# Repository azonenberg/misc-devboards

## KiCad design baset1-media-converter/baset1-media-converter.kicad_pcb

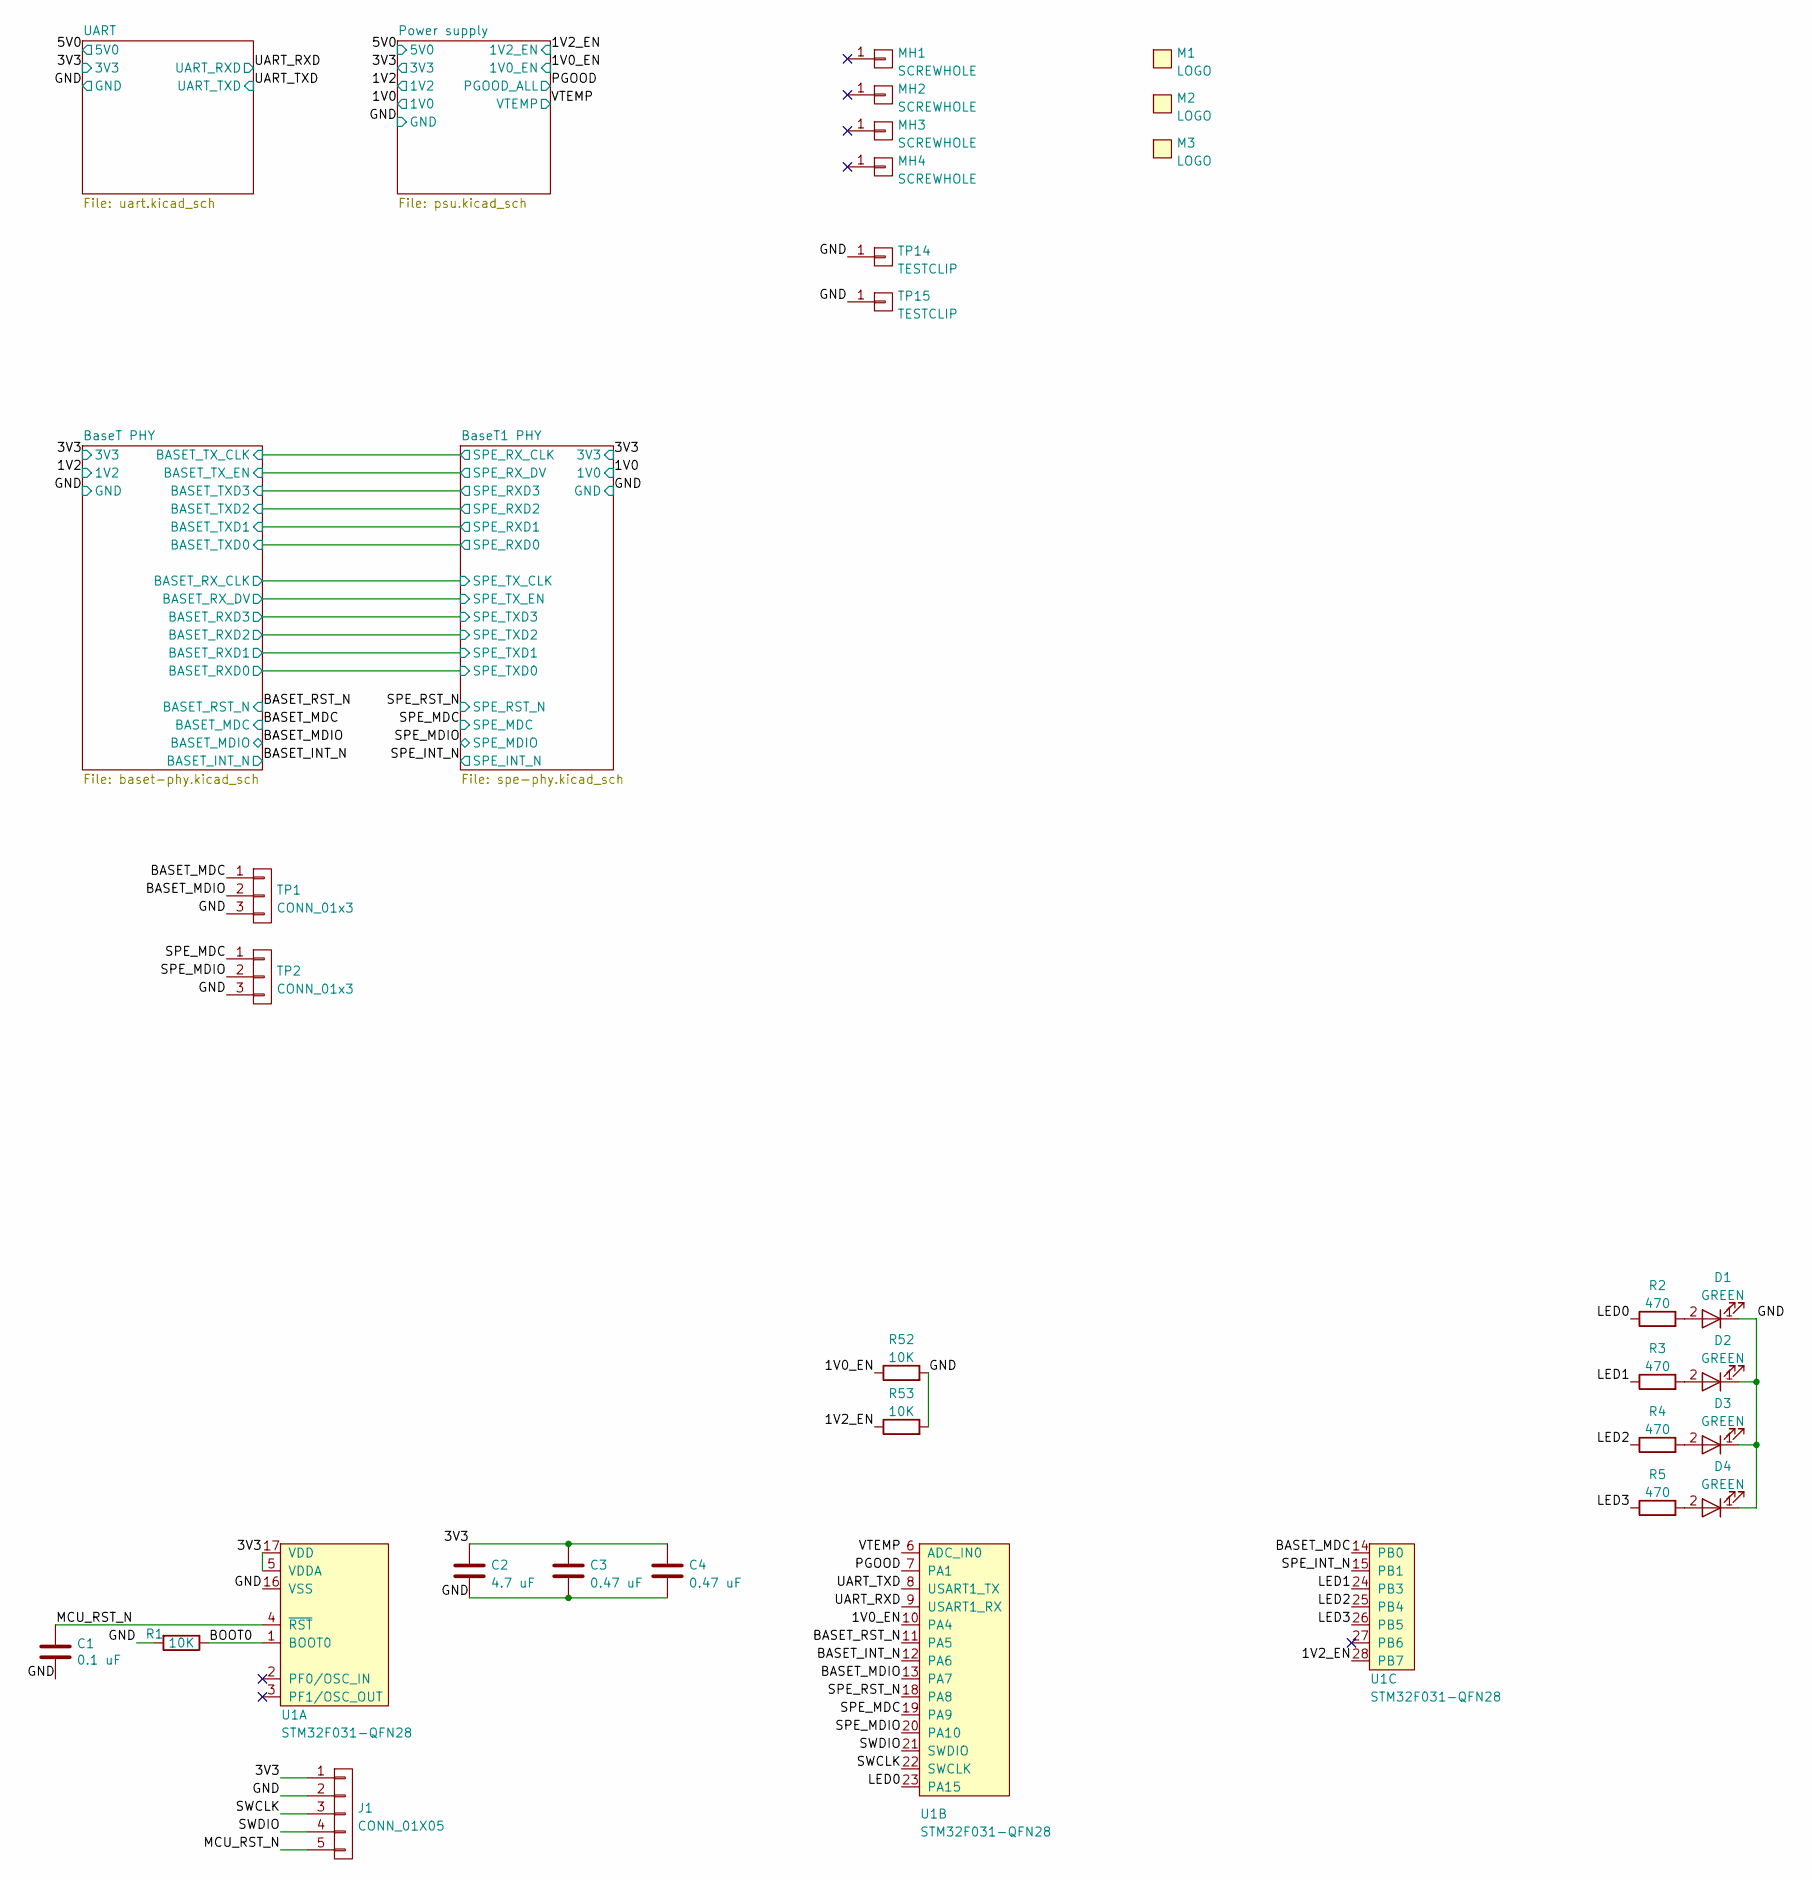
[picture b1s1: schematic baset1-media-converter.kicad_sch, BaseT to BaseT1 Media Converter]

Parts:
C1: 0.1 uF; EIA_0402_CAP_NOSILK
C2: 4.7 uF; EIA_0603_CAP_NOSILK
C3, C4: 0.47 uF; EIA_0402_CAP_NOSILK
D1, D2, D3, D4: GREEN; EIA_0603_LED
J1: CONN_01X05; CONN_HEADER_2.54MM_1x5
M1: LOGO; LONGTHING-1200DPI
M2: LOGO; Logo_silk_WEEE_3.4x5mm
M3: LOGO; Logo_silk_OSHW_6x6mm
MH1, MH2, MH3, MH4: SCREWHOLE; MECHANICAL_CLEARANCEHOLE_4_40
R1, R52, R53: 10K; EIA_0402_RES_NOSILK
R2, R3, R4, R5: 470; EIA_0402_RES_NOSILK
TP1, TP2: CONN_01x3; CONN_HEADER_2.54MM_1x3
TP14, TP15: TESTCLIP; TESTPOINT_SMT_KEYSTONE_5016
U1: STM32F031-QFN28; QFN_28_0.5MM_4x4MM_NOPAD

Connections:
/1V0_EN: R52.1, U1.10 (PA4); also elsewhere on the board
/1V2_EN: R53.1, U1.28 (PB7); also elsewhere on the board
/3V3: C2.1, C3.1, C4.1, J1.1, U1.5 (VDDA), U1.17 (VDD); also elsewhere on the board
/BASET_INT_N: U1.12 (PA6); also elsewhere on the board
/BASET_MDC: TP1.1, U1.14 (PB0); also elsewhere on the board
/BASET_MDIO: TP1.2, U1.13 (PA7); also elsewhere on the board
/BASET_RST_N: U1.11 (PA5); also elsewhere on the board
/BOOT0: R1.1, U1.1 (BOOT0)
/GND: C1.2, C2.2, C3.2, C4.2, D1.1 (K), D2.1 (K), D3.1 (K), D4.1 (K), J1.2, R1.2, R52.2, R53.2, TP1.3, TP2.3, TP14.1, TP15.1, U1.16 (VSS); also elsewhere on the board
/LED0: R2.1, U1.23 (PA15)
/LED1: R3.1, U1.24 (PB3)
/LED2: R4.1, U1.25 (PB4)
/LED3: R5.1, U1.26 (PB5)
/MCU_RST_N: C1.1, J1.5, U1.4 (~RST)
/PGOOD: U1.7 (PA1); also elsewhere on the board
/SPE_INT_N: U1.15 (PB1); also elsewhere on the board
/SPE_MDC: TP2.1, U1.19 (PA9); also elsewhere on the board
/SPE_MDIO: TP2.2, U1.20 (PA10); also elsewhere on the board
/SPE_RST_N: U1.18 (PA8); also elsewhere on the board
/SWCLK: J1.3, U1.22 (PA14)
/SWDIO: J1.4, U1.21 (PA13)
/UART_RXD: U1.9 (PA3); also elsewhere on the board
/UART_TXD: U1.8 (PA2); also elsewhere on the board
/VTEMP: U1.6 (PA0); also elsewhere on the board
unnamed: D1.2 (A), R2.2
unnamed: D2.2 (A), R3.2
unnamed: D3.2 (A), R4.2
unnamed: D4.2 (A), R5.2

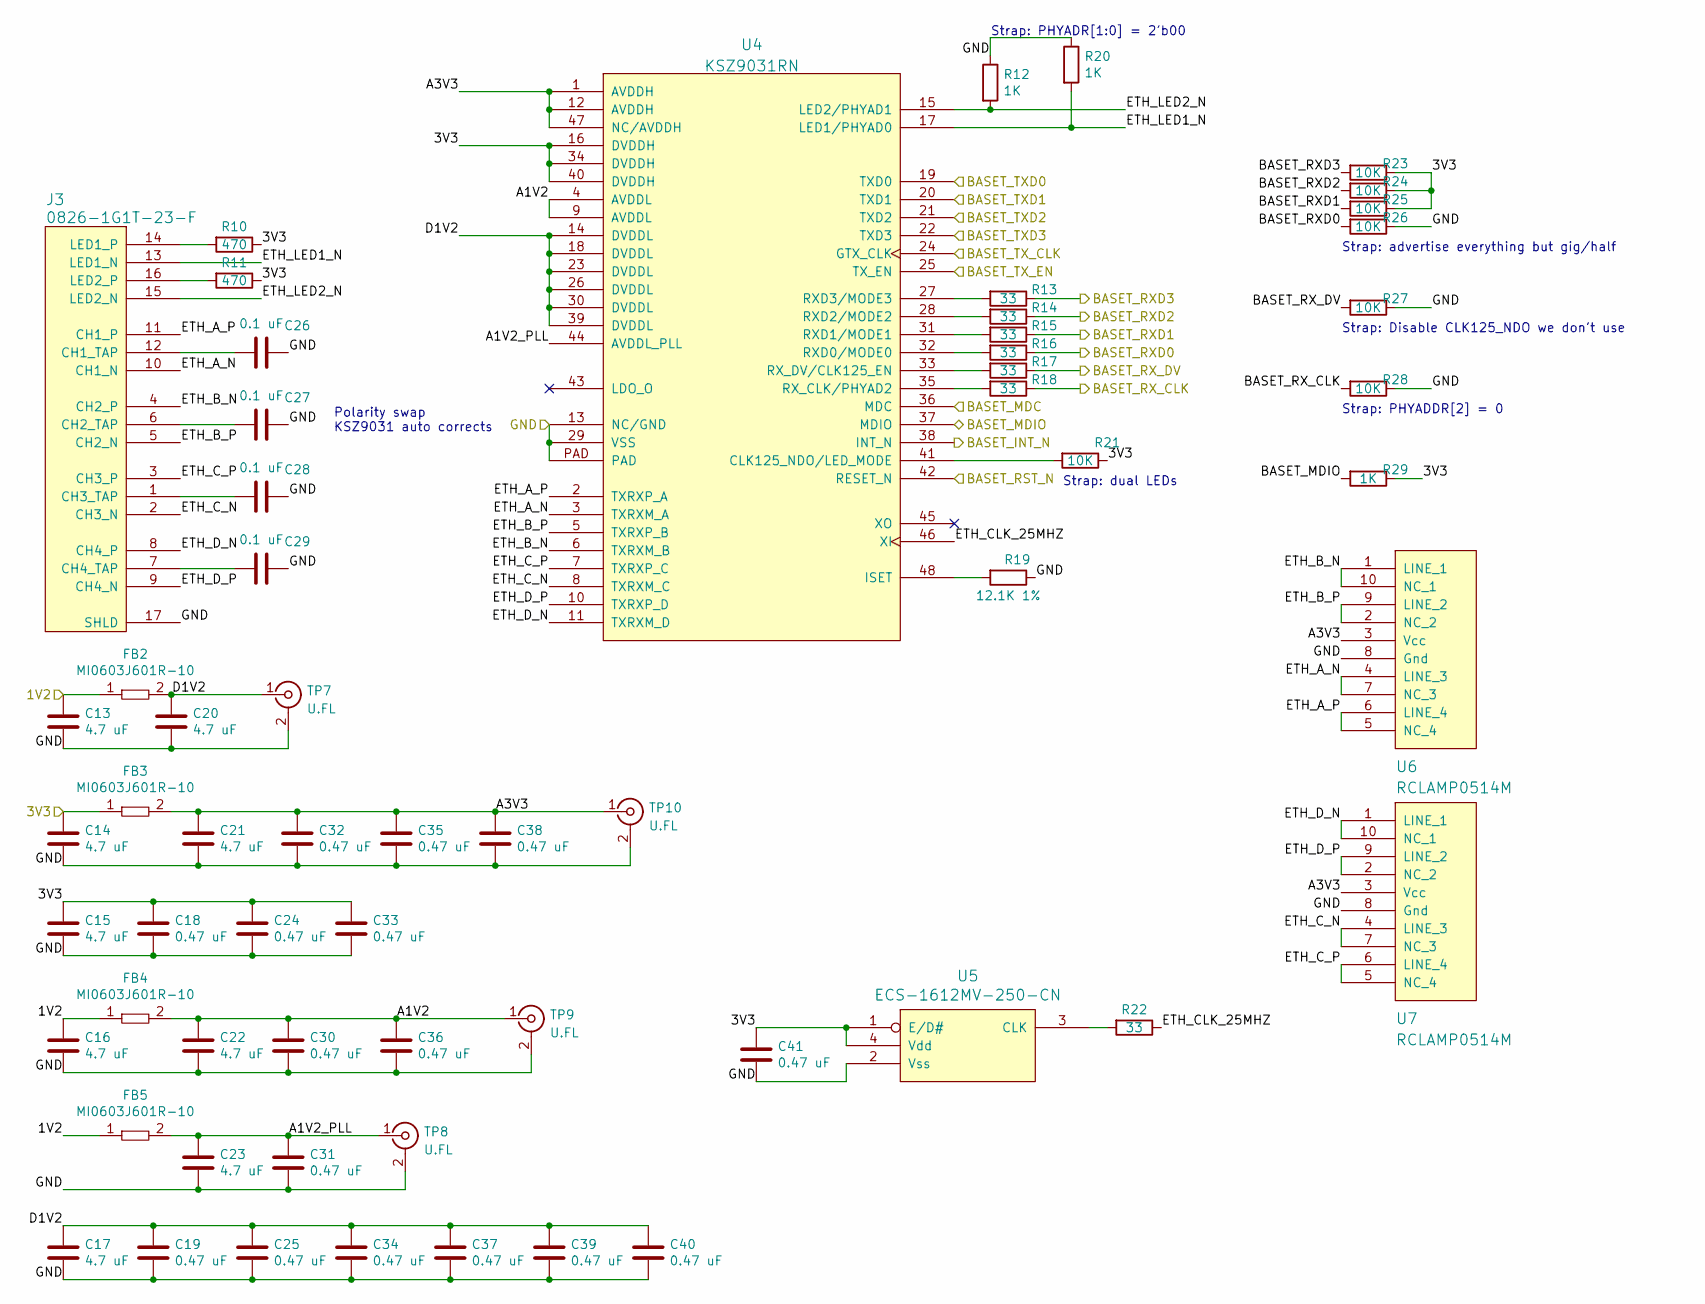
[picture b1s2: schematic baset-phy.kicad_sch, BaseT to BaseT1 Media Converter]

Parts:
C13, C14, C15, C16, C17, C20, C21, C22, C23: 4.7 uF; EIA_0603_CAP_NOSILK
C18, C19, C24, C25, C30, C31, C32, C33, C34, C35, C36, C37, C38, C39, C40, C41: 0.47 uF; EIA_0402_CAP_NOSILK
C26, C27, C28, C29: 0.1 uF; EIA_0402_CAP_NOSILK
FB2, FB3, FB4, FB5: MI0603J601R-10; EIA_0603_INDUCTOR_NOSILK
J3: 0826-1G1T-23-F; CONN_BELFUSE_0826_1G1T_23_F
R10, R11: 470; EIA_0402_RES_NOSILK
R12, R20, R29: 1K; EIA_0402_RES_NOSILK
R13, R14, R15, R16, R17, R18, R22: 33; EIA_0402_RES_NOSILK
R19: 12.1K 1%; EIA_0402_RES_NOSILK
R21, R23, R24, R25, R26, R27, R28: 10K; EIA_0402_RES_NOSILK
TP7, TP8, TP9, TP10: U.FL; CONN_U.FL_TE_1909763-1
U4: KSZ9031RN; QFN_48_0.5MM_7x7MM
U5: ECS-1612MV-250-CN; OSCILLATOR_1.6x1.2
U6, U7: RCLAMP0514M; SOP_10_0.5MM_3MM

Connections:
/1V2: C13.1, C16.1, FB2.1, FB4.1, FB5.1; also elsewhere on the board
/3V3: C14.1, C15.1, C18.1, C24.1, C33.1, C41.1, FB3.1, R10.1, R11.1, R21.1, R23.1, R24.1, R25.1, R29.1, U4.16 (DVDDH), U4.34 (DVDDH), U4.40 (DVDDH), U5.1 (E/D#), U5.4 (Vdd); also elsewhere on the board
/BASET_INT_N: U4.38 (INT_N); also elsewhere on the board
/BASET_MDC: U4.36 (MDC); also elsewhere on the board
/BASET_MDIO: R29.2, U4.37 (MDIO); also elsewhere on the board
/BASET_RST_N: U4.42 (RESET_N); also elsewhere on the board
/BaseT1 PHY/SPE_RXD0: U4.19 (TXD0); also elsewhere on the board
/BaseT1 PHY/SPE_RXD1: U4.20 (TXD1); also elsewhere on the board
/BaseT1 PHY/SPE_RXD2: U4.21 (TXD2); also elsewhere on the board
/BaseT1 PHY/SPE_RX_DV: U4.25 (TX_EN); also elsewhere on the board
/BaseT PHY/A1V2: C22.1, C30.1, C36.1, FB4.2, TP9.1 (In), U4.4 (AVDDL), U4.9 (AVDDL)
/BaseT PHY/A1V2_PLL: C23.1, C31.1, FB5.2, TP8.1 (In), U4.44 (AVDDL_PLL)
/BaseT PHY/A3V3: C21.1, C32.1, C35.1, C38.1, FB3.2, TP10.1 (In), U4.1 (AVDDH), U4.12 (AVDDH), U4.47 (NC/AVDDH), U6.3 (Vcc), U7.3 (Vcc)
/BaseT PHY/BASET_RXD0: R16.1, R26.2; also elsewhere on the board
/BaseT PHY/BASET_RXD1: R15.1, R25.2; also elsewhere on the board
/BaseT PHY/BASET_RXD2: R14.1, R24.2; also elsewhere on the board
/BaseT PHY/BASET_RXD3: R13.1, R23.2; also elsewhere on the board
/BaseT PHY/BASET_RX_CLK: R18.1, R28.2; also elsewhere on the board
/BaseT PHY/BASET_RX_DV: R17.1, R27.2; also elsewhere on the board
/BaseT PHY/BASET_TXD3: U4.22 (TXD3); also elsewhere on the board
/BaseT PHY/BASET_TX_CLK: U4.24 (GTX_CLK); also elsewhere on the board
/BaseT PHY/D1V2: C17.1, C19.1, C20.1, C25.1, C34.1, C37.1, C39.1, C40.1, FB2.2, TP7.1 (In), U4.14 (DVDDL), U4.18 (DVDDL), U4.23 (DVDDL), U4.26 (DVDDL), U4.30 (DVDDL), U4.39 (DVDDL)
/BaseT PHY/ETH_A_N: J3.10 (CH1_N), U4.3 (TXRXM_A), U6.4 (LINE_3), U6.7 (NC_3)
/BaseT PHY/ETH_A_P: J3.11 (CH1_P), U4.2 (TXRXP_A), U6.5 (NC_4), U6.6 (LINE_4)
/BaseT PHY/ETH_B_N: J3.4 (CH2_P), U4.6 (TXRXM_B), U6.1 (LINE_1), U6.10 (NC_1)
/BaseT PHY/ETH_B_P: J3.5 (CH2_N), U4.5 (TXRXP_B), U6.2 (NC_2), U6.9 (LINE_2)
/BaseT PHY/ETH_CLK_25MHZ: R22.1, U4.46 (XI)
/BaseT PHY/ETH_C_N: J3.2 (CH3_N), U4.8 (TXRXM_C), U7.4 (LINE_3), U7.7 (NC_3)
/BaseT PHY/ETH_C_P: J3.3 (CH3_P), U4.7 (TXRXP_C), U7.5 (NC_4), U7.6 (LINE_4)
/BaseT PHY/ETH_D_N: J3.8 (CH4_P), U4.11 (TXRXM_D), U7.1 (LINE_1), U7.10 (NC_1)
/BaseT PHY/ETH_D_P: J3.9 (CH4_N), U4.10 (TXRXP_D), U7.2 (NC_2), U7.9 (LINE_2)
/BaseT PHY/ETH_LED1_N: J3.13 (LED1_N), R20.2, U4.17 (LED1/PHYAD0)
/BaseT PHY/ETH_LED2_N: J3.15 (LED2_N), R12.2, U4.15 (LED2/PHYAD1)
/GND: C13.2, C14.2, C15.2, C16.2, C17.2, C18.2, C19.2, C20.2, C21.2, C22.2, C23.2, C24.2, C25.2, C26.1, C27.1, C28.1, C29.1, C30.2, C31.2, C32.2, C33.2, C34.2, C35.2, C36.2, C37.2, C38.2, C39.2, C40.2, C41.2, J3.17 (SHLD), R12.1, R19.1, R20.1, R26.1, R27.1, R28.1, TP7.2 (Ext), TP8.2 (Ext), TP9.2 (Ext), TP10.2 (Ext), U4.13 (NC/GND), U4.29 (VSS), U4.PAD, U5.2 (Vss), U6.8 (Gnd), U7.8 (Gnd); also elsewhere on the board
unnamed: C26.2, J3.12 (CH1_TAP)
unnamed: C27.2, J3.6 (CH2_TAP)
unnamed: C28.2, J3.1 (CH3_TAP)
unnamed: C29.2, J3.7 (CH4_TAP)
unnamed: J3.14 (LED1_P), R10.2
unnamed: J3.16 (LED2_P), R11.2
unnamed: R13.2, U4.27 (RXD3/MODE3)
unnamed: R14.2, U4.28 (RXD2/MODE2)
unnamed: R15.2, U4.31 (RXD1/MODE1)
unnamed: R16.2, U4.32 (RXD0/MODE0)
unnamed: R17.2, U4.33 (RX_DV/CLK125_EN)
unnamed: R18.2, U4.35 (RX_CLK/PHYAD2)
unnamed: R19.2, U4.48 (ISET)
unnamed: R21.2, U4.41 (CLK125_NDO/LED_MODE)
unnamed: R22.2, U5.3 (CLK)

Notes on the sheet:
Strap: advertise everything but gig/half
Strap: Disable CLK125_NDO we don't use
Strap: dual LEDs
Strap: PHYADDR[2] = 0
Polarity swap KSZ9031 auto corrects
Strap: PHYADR[1:0] = 2'b00

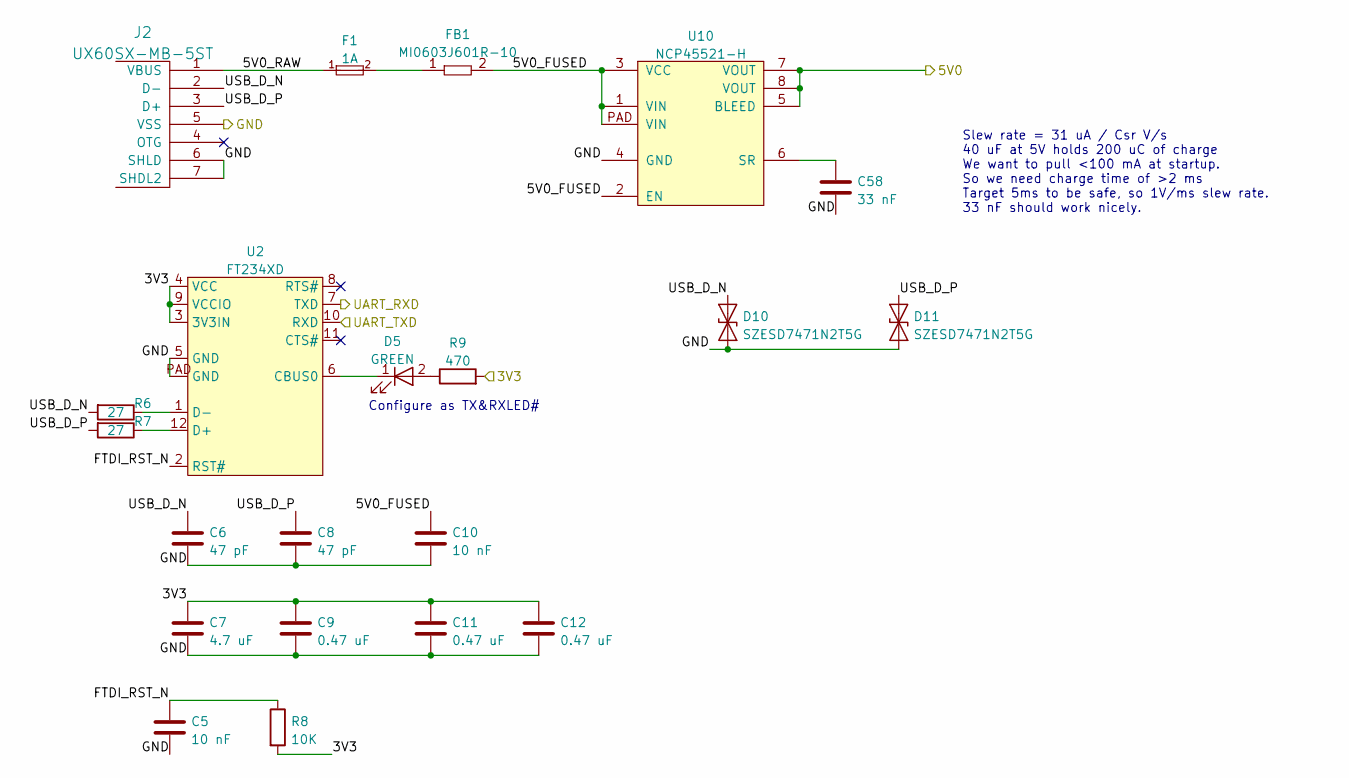
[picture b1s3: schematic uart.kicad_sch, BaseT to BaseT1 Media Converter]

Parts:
C5, C10: 10 nF; EIA_0603_CAP_NOSILK
C6, C8: 47 pF; EIA_0402_CAP_NOSILK
C7: 4.7 uF; EIA_0603_CAP_NOSILK
C9, C11, C12: 0.47 uF; EIA_0402_CAP_NOSILK
C58: 33 nF; EIA_0402_CAP_NOSILK
D5: GREEN; EIA_0603_LED
D10, D11: SZESD7471N2T5G; SOD882
F1: 1A; EIA_0402_RES_NOSILK
FB1: MI0603J601R-10; EIA_0603_INDUCTOR_NOSILK
J2: UX60SX-MB-5ST; CONN_HIROSE_UX60S-MB-5ST_MINI_USB
R6, R7: 27; EIA_0402_RES_NOSILK
R8: 10K; EIA_0402_RES_NOSILK
R9: 470; EIA_0402_RES_NOSILK
U2: FT234XD; DFN_12_0.5MM_3x3MM
U10: NCP45521-H; DFN_8_0.5MM_2x2MM

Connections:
/3V3: C7.1, C9.1, C11.1, C12.1, R8.2, R9.2, U2.3 (3V3IN), U2.4 (VCC), U2.9 (VCCIO); also elsewhere on the board
/5V0: U10.5 (BLEED), U10.7 (VOUT), U10.8 (VOUT); also elsewhere on the board
/GND: C5.2, C6.2, C7.2, C8.2, C9.2, C10.2, C11.2, C12.2, C58.2, D10.1 (A1), D11.1 (A1), J2.5 (VSS), J2.6 (SHLD), J2.7 (SHDL2), U2.5 (GND), U2.PAD (GND), U10.4 (GND); also elsewhere on the board
/UART/5V0_FUSED: C10.1, FB1.2, U10.1 (VIN), U10.2 (EN), U10.3 (VCC), U10.PAD (VIN)
/UART/5V0_RAW: F1.1, J2.1 (VBUS)
/UART/FTDI_RST_N: C5.1, R8.1, U2.2 (RST#)
/UART/USB_D_N: C6.1, D10.2 (A2), J2.2 (D-), R6.2
/UART/USB_D_P: C8.1, D11.2 (A2), J2.3 (D+), R7.2
/UART_RXD: U2.7 (TXD); also elsewhere on the board
/UART_TXD: U2.10 (RXD); also elsewhere on the board
unnamed: C58.1, U10.6 (SR)
unnamed: D5.1 (K), U2.6 (CBUS0)
unnamed: D5.2 (A), R9.1
unnamed: F1.2, FB1.1
unnamed: R6.1, U2.1 (D-)
unnamed: R7.1, U2.12 (D+)

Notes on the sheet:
Configure as TX&RXLED#
Slew rate = 31 uA / Csr V/s 40 uF at 5V holds 200 uC of charge We want to pull <100 mA at startup. So we need charge time of >2 ms Target 5ms to be safe, so 1V/ms slew rate. 33 nF should work nicely.

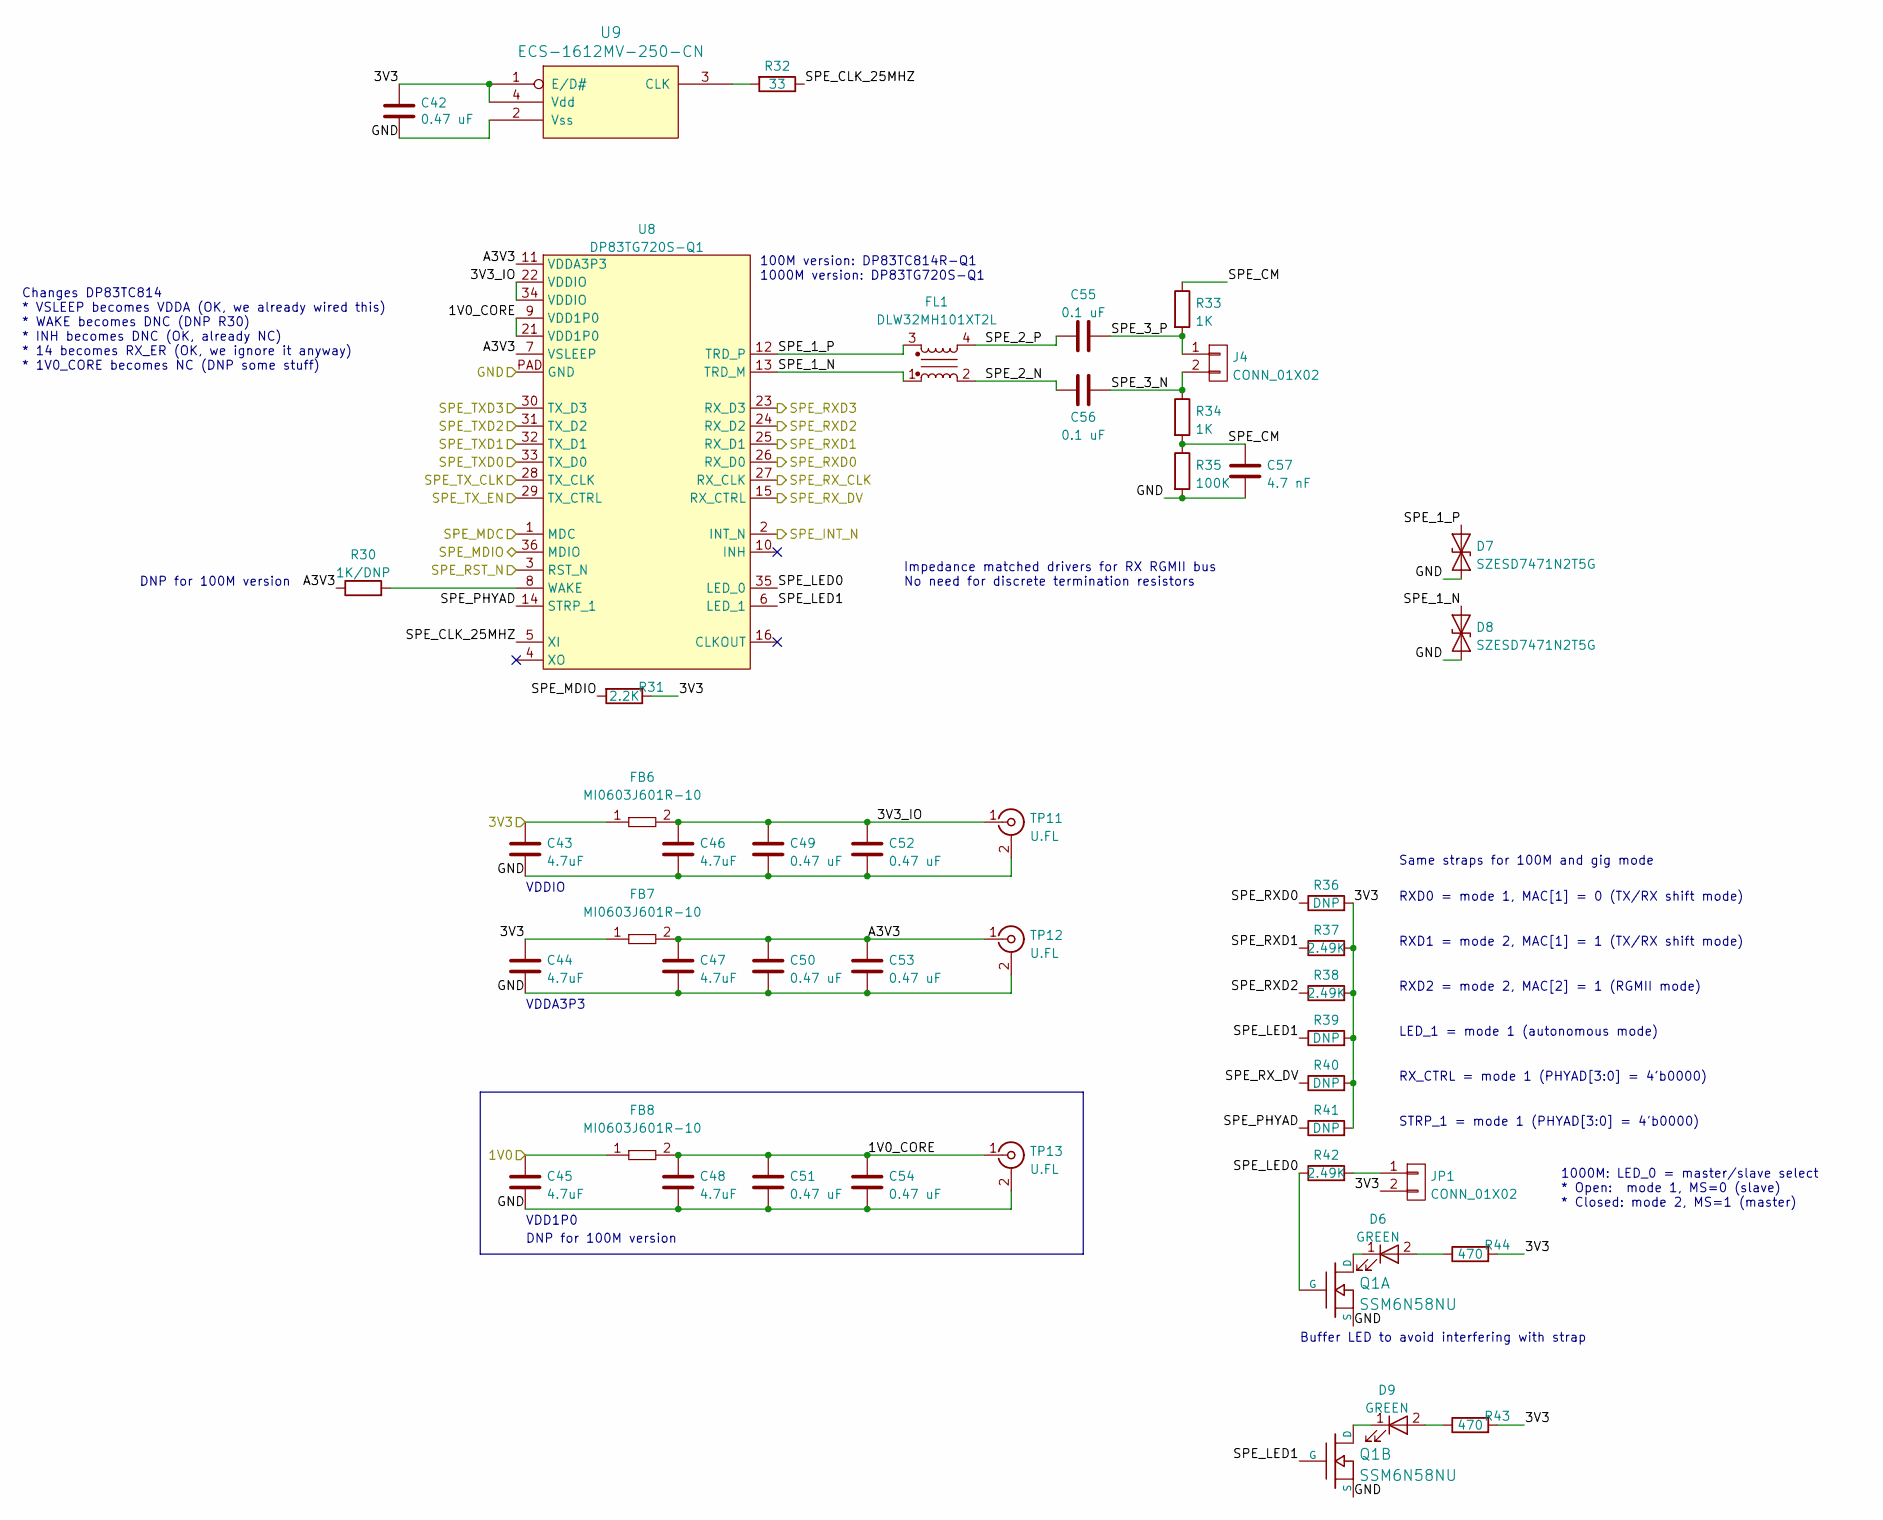
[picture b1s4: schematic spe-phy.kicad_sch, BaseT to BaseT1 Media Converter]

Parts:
C42, C49, C50, C51, C52, C53, C54: 0.47 uF; EIA_0402_CAP_NOSILK
C43, C44, C45, C46, C47, C48: 4.7uF; EIA_0603_CAP_NOSILK
C55, C56: 0.1 uF; EIA_0402_CAP_NOSILK
C57: 4.7 nF; EIA_0603_CAP_NOSILK
D6, D9: GREEN; EIA_0603_LED
D7, D8: SZESD7471N2T5G; SOD882
FB6, FB7, FB8: MI0603J601R-10; EIA_0603_INDUCTOR_NOSILK
FL1: DLW32MH101XT2L; CMC_1210
J4: CONN_01X02; CONN_HEADER_2.54MM_1x2
JP1: CONN_01X02; CONN_HEADER_2.54MM_1x2
Q1: SSM6N58NU; DFN_6_0.65MM_2x2MM_GDS
R30: 1K/DNP; EIA_0402_RES_NOSILK
R31: 2.2K; EIA_0402_RES_NOSILK
R32: 33; EIA_0402_RES_NOSILK
R33, R34: 1K; EIA_0402_RES_NOSILK
R35: 100K; EIA_0402_RES_NOSILK
R36, R39, R40, R41: DNP; EIA_0402_RES_NOSILK
R37, R38, R42: 2.49K; EIA_0402_RES_NOSILK
R43, R44: 470; EIA_0402_RES_NOSILK
TP11, TP12, TP13: U.FL; CONN_U.FL_TE_1909763-1
U8: DP83TG720S-Q1; QFN_36_0.5MM_6x6MM
U9: ECS-1612MV-250-CN; OSCILLATOR_1.6x1.2

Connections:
/1V0: C45.1, FB8.1; also elsewhere on the board
/3V3: C42.1, C43.1, C44.1, FB6.1, FB7.1, JP1.2, R31.1, R36.2, R37.2, R38.2, R39.2, R40.2, R41.2, R43.2, R44.2, U9.1 (E/D#), U9.4 (Vdd); also elsewhere on the board
/BaseT1 PHY/1V0_CORE: C48.1, C51.1, C54.1, FB8.2, TP13.1 (In), U8.9 (VDD1P0), U8.21 (VDD1P0)
/BaseT1 PHY/3V3_IO: C46.1, C49.1, C52.1, FB6.2, TP11.1 (In), U8.22 (VDDIO), U8.34 (VDDIO)
/BaseT1 PHY/A3V3: C47.1, C50.1, C53.1, FB7.2, R30.1, TP12.1 (In), U8.7 (VSLEEP), U8.11 (VDDA3P3)
/BaseT1 PHY/SPE_1_N: D8.2 (A2), FL1.1, U8.13 (TRD_M)
/BaseT1 PHY/SPE_1_P: D7.2 (A2), FL1.3, U8.12 (TRD_P)
/BaseT1 PHY/SPE_2_N: C56.1, FL1.2
/BaseT1 PHY/SPE_2_P: C55.1, FL1.4
/BaseT1 PHY/SPE_3_N: C56.2, J4.2, R34.1
/BaseT1 PHY/SPE_3_P: C55.2, J4.1, R33.2
/BaseT1 PHY/SPE_CLK_25MHZ: R32.1, U8.5 (XI)
/BaseT1 PHY/SPE_CM: C57.1, R33.1, R34.2, R35.1
/BaseT1 PHY/SPE_LED0: Q1.G1 (G), R42.1, U8.35 (LED_0)
/BaseT1 PHY/SPE_LED1: Q1.G2 (G), R39.1, U8.6 (LED_1)
/BaseT1 PHY/SPE_PHYAD: R41.1, U8.14 (STRP_1)
/BaseT1 PHY/SPE_RXD0: R36.1, U8.26 (RX_D0); also elsewhere on the board
/BaseT1 PHY/SPE_RXD1: R37.1, U8.25 (RX_D1); also elsewhere on the board
/BaseT1 PHY/SPE_RXD2: R38.1, U8.24 (RX_D2); also elsewhere on the board
/BaseT1 PHY/SPE_RX_DV: R40.1, U8.15 (RX_CTRL); also elsewhere on the board
/BaseT PHY/BASET_RXD0: U8.33 (TX_D0); also elsewhere on the board
/BaseT PHY/BASET_RXD1: U8.32 (TX_D1); also elsewhere on the board
/BaseT PHY/BASET_RXD2: U8.31 (TX_D2); also elsewhere on the board
/BaseT PHY/BASET_RXD3: U8.30 (TX_D3); also elsewhere on the board
/BaseT PHY/BASET_RX_CLK: U8.28 (TX_CLK); also elsewhere on the board
/BaseT PHY/BASET_RX_DV: U8.29 (TX_CTRL); also elsewhere on the board
/BaseT PHY/BASET_TXD3: U8.23 (RX_D3); also elsewhere on the board
/BaseT PHY/BASET_TX_CLK: U8.27 (RX_CLK); also elsewhere on the board
/GND: C42.2, C43.2, C44.2, C45.2, C46.2, C47.2, C48.2, C49.2, C50.2, C51.2, C52.2, C53.2, C54.2, C57.2, D7.1 (A1), D8.1 (A1), Q1.S1 (S), Q1.S2 (S), R35.2, TP11.2 (Ext), TP12.2 (Ext), TP13.2 (Ext), U8.PAD (GND), U9.2 (Vss); also elsewhere on the board
/SPE_INT_N: U8.2 (INT_N); also elsewhere on the board
/SPE_MDC: U8.1 (MDC); also elsewhere on the board
/SPE_MDIO: R31.2, U8.36 (MDIO); also elsewhere on the board
/SPE_RST_N: U8.3 (RST_N); also elsewhere on the board
unnamed: D6.1 (K), Q1.D1 (D)
unnamed: D6.2 (A), R44.1
unnamed: D9.1 (K), Q1.D2 (D)
unnamed: D9.2 (A), R43.1
unnamed: JP1.1, R42.2
unnamed: R30.2, U8.8 (WAKE)
unnamed: R32.2, U9.3 (CLK)

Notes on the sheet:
Changes DP83TC814 * VSLEEP becomes VDDA (OK, we already wired this) * WAKE becomes DNC (DNP R30) * INH becomes DNC (OK, already NC) * 14 becomes RX_ER (OK, we ignore it anyway) * 1V0_CORE becomes NC (DNP some stuff)
Same straps for 100M and gig mode
RXD2 = mode 2, MAC[2] = 1 (RGMII mode)
RXD1 = mode 2, MAC[1] = 1 (TX/RX shift mode)
LED_1 = mode 1 (autonomous mode)
STRP_1 = mode 1 (PHYAD[3:0] = 4'b0000)
DNP for 100M version
1000M: LED_0 = master/slave select * Open: mode 1, MS=0 (slave) * Closed: mode 2, MS=1 (master)
Impedance matched drivers for RX RGMII bus No need for discrete termination resistors
VDDIO
100M version: DP83TC814R-Q1 1000M version: DP83TG720S-Q1
VDD1P0
Buffer LED to avoid interfering with strap
RX_CTRL = mode 1 (PHYAD[3:0] = 4'b0000)
VDDA3P3
RXD0 = mode 1, MAC[1] = 0 (TX/RX shift mode)

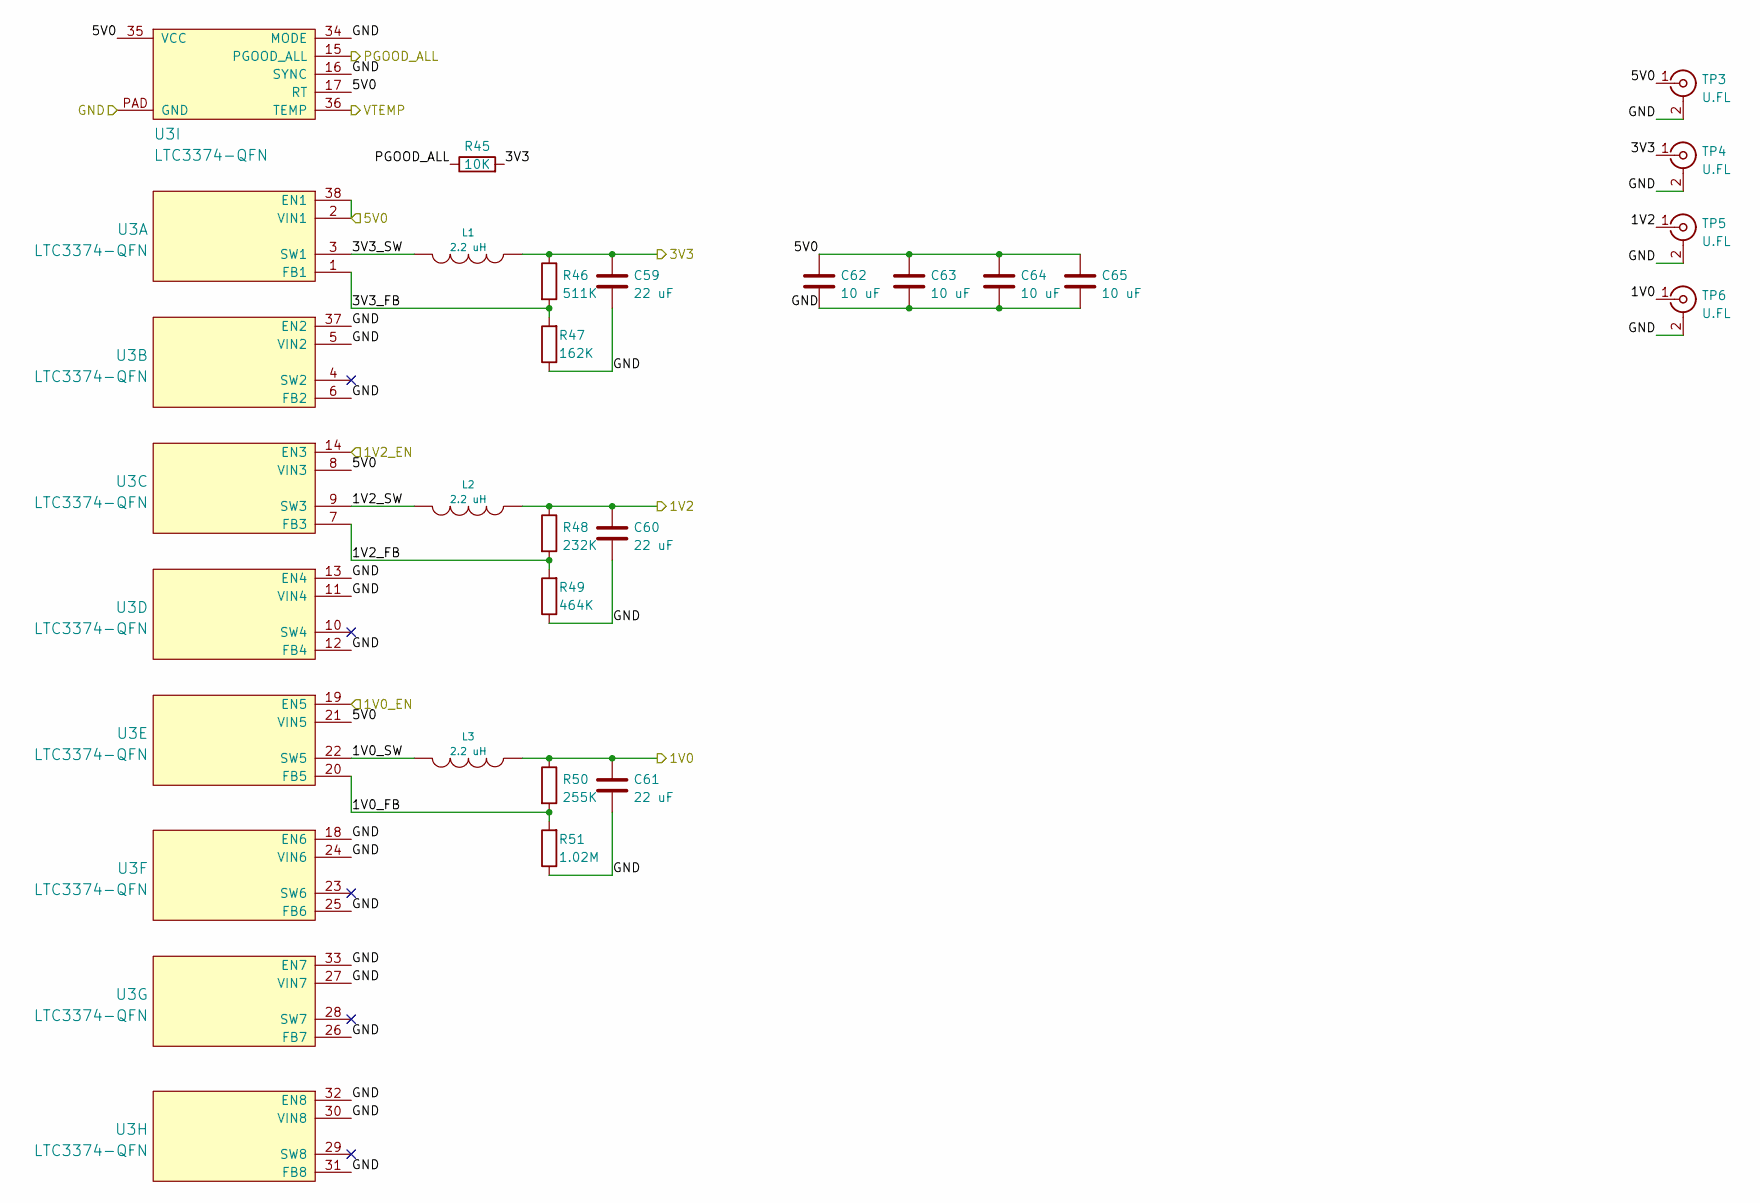
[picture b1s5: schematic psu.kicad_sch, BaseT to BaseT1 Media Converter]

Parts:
C59, C60, C61: 22 uF; EIA_1210_CAP_NOSILK
C62, C63, C64, C65: 10 uF; EIA_1206_CAP_NOSILK
L1, L2, L3: 2.2 uH; INDUCTOR_YUDEN_NRS5030
R45: 10K; EIA_0402_RES_NOSILK
R46: 511K; EIA_0402_RES_NOSILK
R47: 162K; EIA_0402_RES_NOSILK
R48: 232K; EIA_0402_RES_NOSILK
R49: 464K; EIA_0402_RES_NOSILK
R50: 255K; EIA_0402_RES_NOSILK
R51: 1.02M; EIA_0402_RES_NOSILK
TP3, TP4, TP5, TP6: U.FL; CONN_U.FL_TE_1909763-1
U3: LTC3374-QFN; QFN_38_0.5MM_5x7MM

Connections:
/1V0: C61.1, L3.1, R50.1, TP6.1 (In); also elsewhere on the board
/1V0_EN: U3.19 (EN5); also elsewhere on the board
/1V2: C60.1, L2.1, R48.1, TP5.1 (In); also elsewhere on the board
/1V2_EN: U3.14 (EN3); also elsewhere on the board
/3V3: C59.1, L1.1, R45.2, R46.1, TP4.1 (In); also elsewhere on the board
/5V0: C62.1, C63.1, C64.1, C65.1, TP3.1 (In), U3.2 (VIN1), U3.8 (VIN3), U3.17 (RT), U3.21 (VIN5), U3.35 (VCC), U3.38 (EN1); also elsewhere on the board
/GND: C59.2, C60.2, C61.2, C62.2, C63.2, C64.2, C65.2, R47.1, R49.1, R51.1, TP3.2 (Ext), TP4.2 (Ext), TP5.2 (Ext), TP6.2 (Ext), U3.5 (VIN2), U3.6 (FB2), U3.11 (VIN4), U3.12 (FB4), U3.13 (EN4), U3.16 (SYNC), U3.18 (EN6), U3.24 (VIN6), U3.25 (FB6), U3.26 (FB7), U3.27 (VIN7), U3.30 (VIN8), U3.31 (FB8), U3.32 (EN8), U3.33 (EN7), U3.34 (MODE), U3.37 (EN2), U3.PAD (GND); also elsewhere on the board
/PGOOD: R45.1, U3.15 (PGOOD_ALL); also elsewhere on the board
/Power supply/1V0_FB: R50.2, R51.2, U3.20 (FB5)
/Power supply/1V0_SW: L3.2, U3.22 (SW5)
/Power supply/1V2_FB: R48.2, R49.2, U3.7 (FB3)
/Power supply/1V2_SW: L2.2, U3.9 (SW3)
/Power supply/3V3_FB: R46.2, R47.2, U3.1 (FB1)
/Power supply/3V3_SW: L1.2, U3.3 (SW1)
/VTEMP: U3.36 (TEMP); also elsewhere on the board

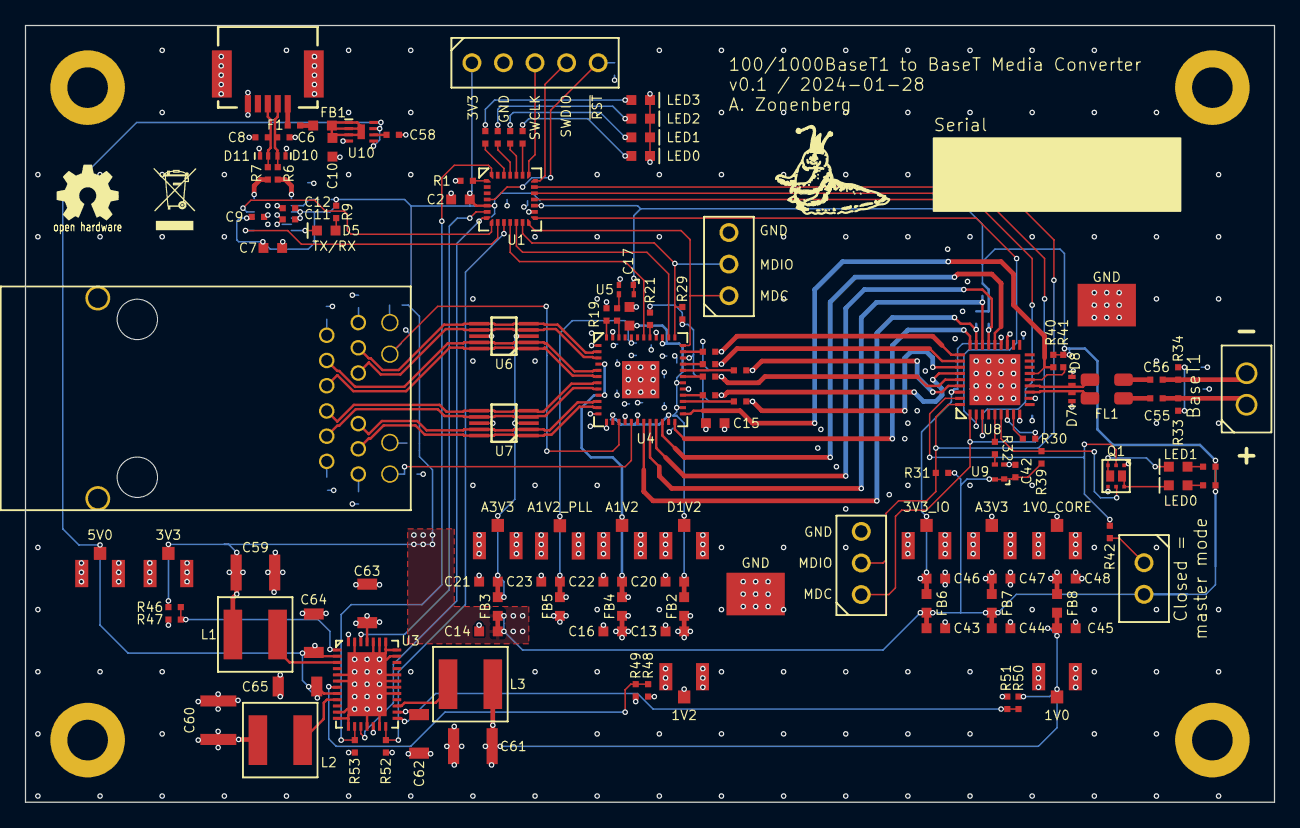
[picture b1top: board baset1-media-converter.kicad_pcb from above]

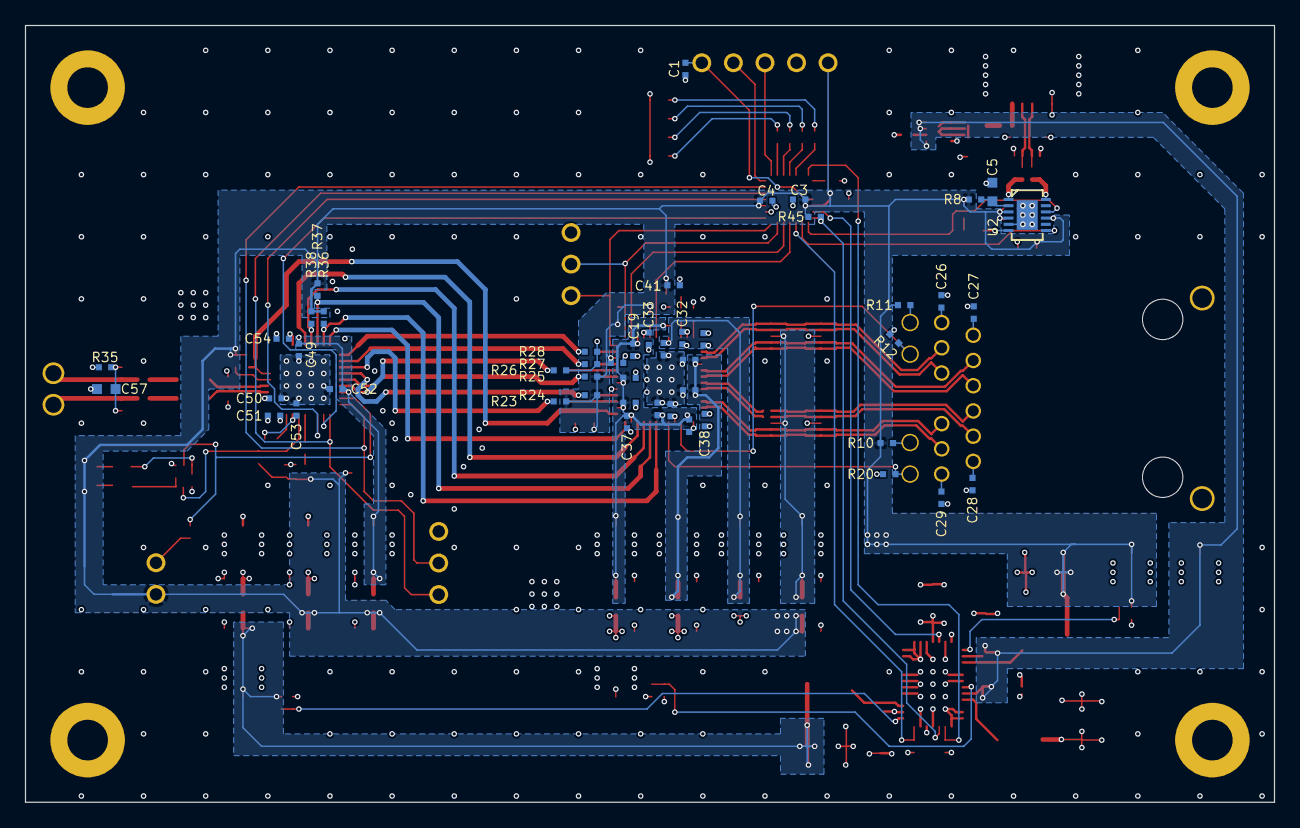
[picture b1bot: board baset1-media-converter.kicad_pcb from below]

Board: 4 copper layers, 100.5 x 62.5 mm, 180 parts (48 on the bottom side), 111 nets.
